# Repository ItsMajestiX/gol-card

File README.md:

# Game of Life Card
A custom PCB that uses a TI MSP430 MCU to run a finite version of Conway's Game of Life on an ePaper display.
# Documentation
To read about the development of this project, please visit [this project's site](https://itsmajestix.github.io/gol-card/). If you want to view the site's source, go to the `gol_card_docs` directory to find many markdown files documenting the development process of this project.
# Building
This project will build on Zig 0.14.1. Once you have downloaded it, run `zig build run` to try out the desktop simulator.

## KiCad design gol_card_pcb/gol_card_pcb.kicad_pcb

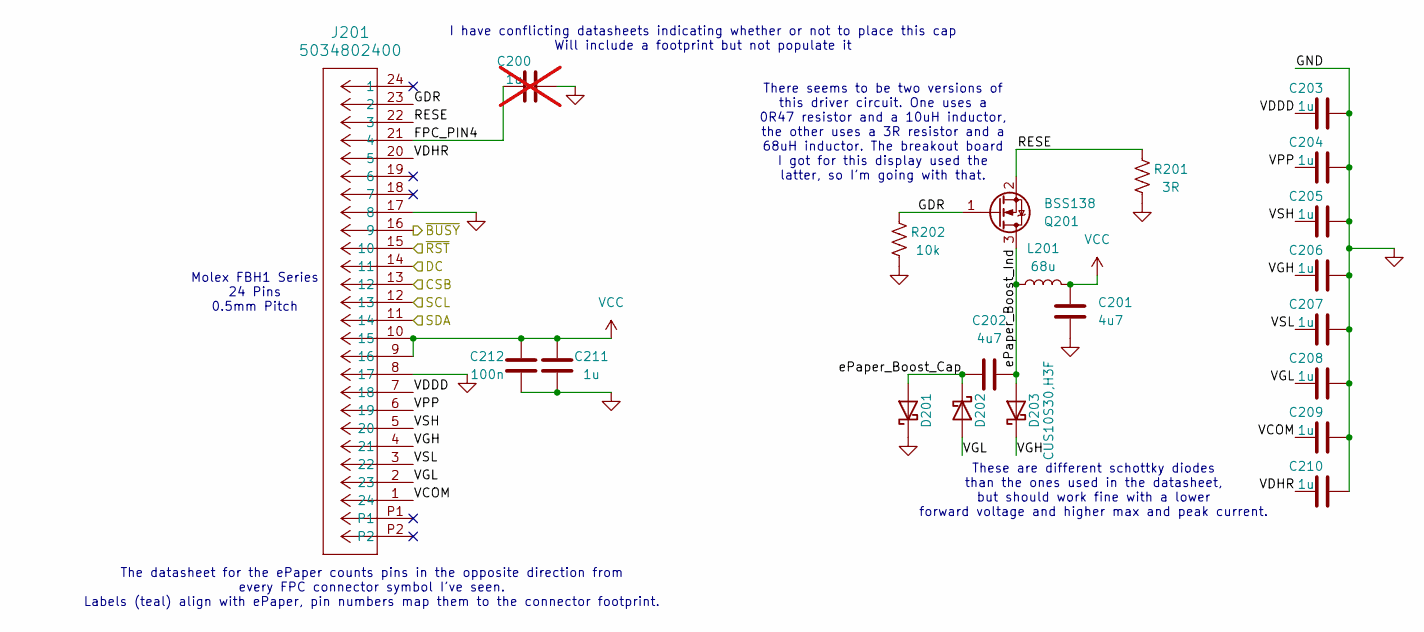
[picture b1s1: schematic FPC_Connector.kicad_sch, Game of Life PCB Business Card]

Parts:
C200: 1u; C_0603_1608Metric; not fitted
C201, C202: 4u7; C_0805_2012Metric
C203, C204, C205, C206, C207, C208, C209, C210, C211: 1u; C_0603_1608Metric
C212: 100n; C_0603_1608Metric
D201, D202, D203: CUS10S30,H3F; D_SOD-323
J201: 5034802400; CON_5034802400_MOL
L201: 68u; L_Taiyo-Yuden_NR-80xx
Q201: BSS138; SOT-23
R201: 3R; R_0805_2012Metric
R202: 10k; R_0402_1005Metric

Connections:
/FPC_Connector/CSB: J201.13 (12); also elsewhere on the board
/FPC_Connector/DC: J201.14 (11); also elsewhere on the board
/FPC_Connector/FPC_PIN4: C200.1, J201.21 (4)
/FPC_Connector/GDR: J201.23 (2), Q201.1 (G), R202.2
/FPC_Connector/RESE: J201.22 (3), Q201.2 (S), R201.1
/FPC_Connector/SCL: J201.12 (13); also elsewhere on the board
/FPC_Connector/SDA: J201.11 (14); also elsewhere on the board
/FPC_Connector/VCOM: C209.1, J201.1 (24)
/FPC_Connector/VDDD: C203.1, J201.7 (18)
/FPC_Connector/VDHR: C210.1, J201.20 (5)
/FPC_Connector/VGH: C206.1, D203.1 (K), J201.4 (21)
/FPC_Connector/VGL: C208.1, D202.2 (A), J201.2 (23)
/FPC_Connector/VPP: C204.1, J201.6 (19)
/FPC_Connector/VSH: C205.1, J201.5 (20)
/FPC_Connector/VSL: C207.1, J201.3 (22)
/FPC_Connector/ePaper_Boost_Cap: C202.2, D201.2 (A), D202.1 (K)
/FPC_Connector/ePaper_Boost_Ind: C202.1, D203.2 (A), L201.1, Q201.3 (D)
/FPC_Connector/~BUSY: J201.16 (9); also elsewhere on the board
/FPC_Connector/~RST: J201.15 (10); also elsewhere on the board
GND: C200.2, C201.2, C203.2, C204.2, C205.2, C206.2, C207.2, C208.2, C209.2, C210.2, C211.2, C212.2, D201.1 (K), J201.8 (17), J201.17 (8), R201.2, R202.1; also elsewhere on the board
VCC: C201.1, C211.1, C212.1, J201.9 (16), J201.10 (15), L201.2; also elsewhere on the board

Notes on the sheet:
The datasheet for the ePaper counts pins in the opposite direction from every FPC connector symbol I've seen. Labels (teal) align with ePaper, pin numbers map them to the connector footprint.
Molex FBH1 Series 24 Pins 0.5mm Pitch
These are different schottky diodes than the ones used in the datasheet, but should work fine with a lower forward voltage and higher max and peak current.
There seems to be two versions of this driver circuit. One uses a 0R47 resistor and a 10uH inductor, the other uses a 3R resistor and a 68uH inductor. The breakout board I got for this display used the latter, so I'm going with that.
I have conflicting datasheets indicating whether or not to place this cap Will include a footprint but not populate it

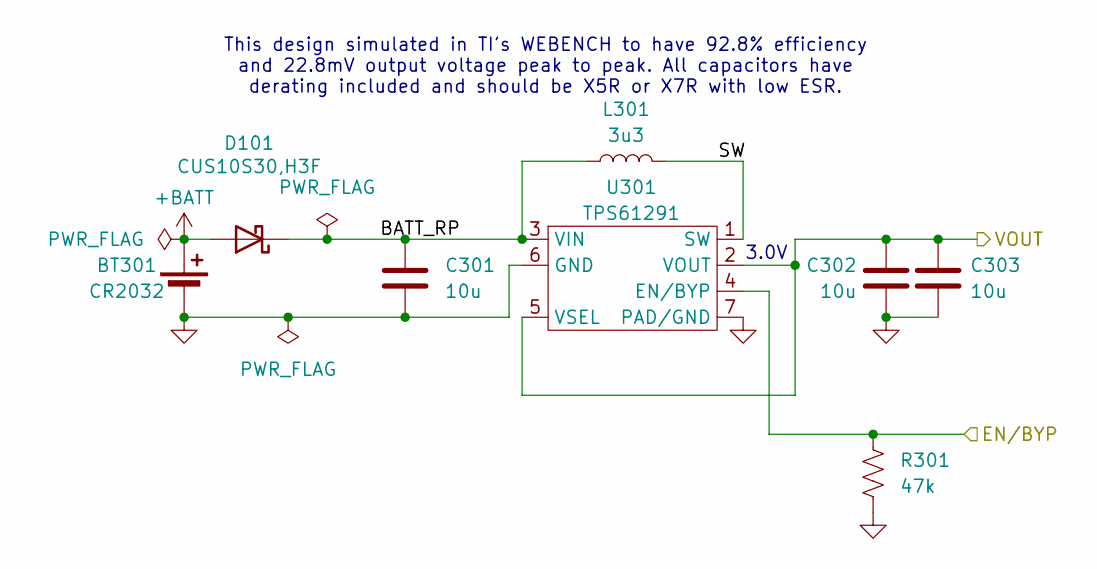
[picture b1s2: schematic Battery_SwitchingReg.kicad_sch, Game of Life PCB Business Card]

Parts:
BT301: CR2032; BatteryHolder_Keystone_3002_1x2032
C301, C302, C303: 10u; C_0603_1608Metric
D101: CUS10S30,H3F; D_SOD-323
L301: 3u3; L_Taiyo-Yuden_NR-50xx
R301: 47k; R_0402_1005Metric
U301: TPS61291; WSON-6-1EP_2x2mm_P0.65mm_EP1x1.6mm

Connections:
+BATT: BT301.1 (+), D101.2 (A)
/Battery_SwitchingReg/BATT_RP: C301.1, D101.1 (K), L301.1, U301.3 (VIN)
/Battery_SwitchingReg/EN/BYP: R301.1, U301.4 (EN/BYP); also elsewhere on the board
/Battery_SwitchingReg/SW: L301.2, U301.1 (SW)
/MCU/PWR_BOARD: C302.1, C303.1, U301.2 (VOUT), U301.5 (VSEL); also elsewhere on the board
GND: BT301.2 (-), C301.2, C302.2, C303.2, R301.2, U301.6 (GND), U301.7 (PAD/GND); also elsewhere on the board

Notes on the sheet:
3.0V
This design simulated in TI's WEBENCH to have 92.8% efficiency and 22.8mV output voltage peak to peak. All capacitors have derating included and should be X5R or X7R with low ESR.

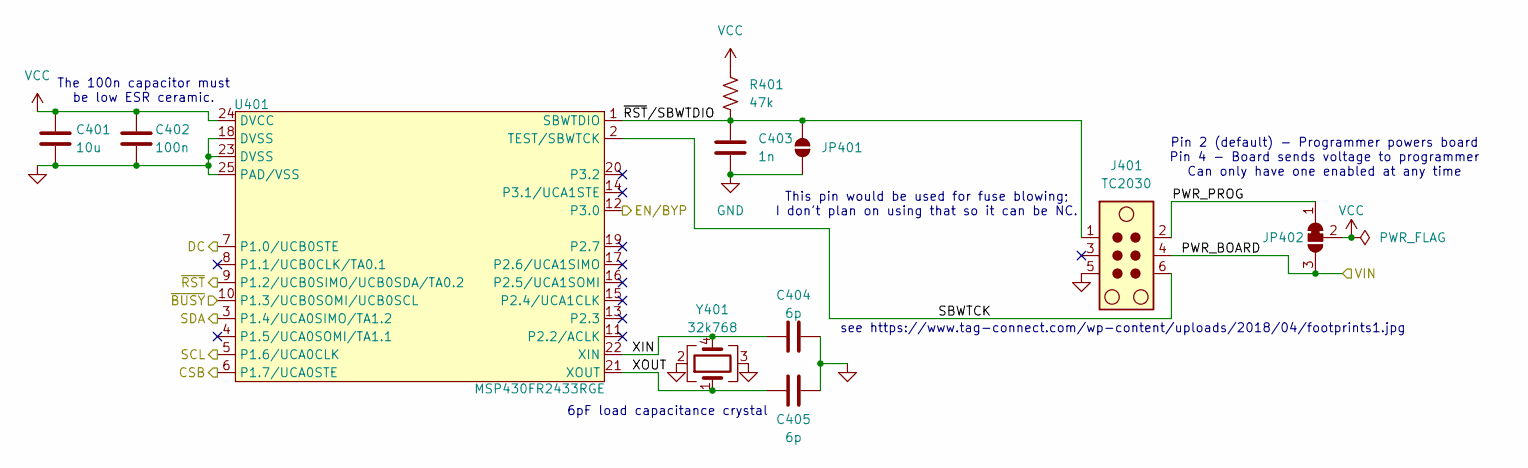
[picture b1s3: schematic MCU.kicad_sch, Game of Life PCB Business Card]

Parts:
C401: 10u; C_0603_1608Metric
C402: 100n; C_0603_1608Metric
C403: 1n; C_0402_1005Metric
C404, C405: 6p; C_0402_1005Metric
J401: TC2030; TC2030_Legs_PTH
JP401: SolderJumper_2_Open; SolderJumper-2_P1.3mm_Open_TrianglePad1.0x1.5mm
JP402: SolderJumper_3_Bridged12; SolderJumper-3_P1.3mm_Bridged12_Pad1.0x1.5mm_NumberLabels
R401: 47k; R_0402_1005Metric
U401: MSP430FR2433RGE; Texas_RGE0024H_VQFN-24-1EP_4x4mm_P0.5mm_EP2.7x2.7mm
Y401: 32k768; Crystal_SMD_Abracon_ABS25-4Pin_8.0x3.8mm

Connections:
/Battery_SwitchingReg/EN/BYP: U401.12 (P3.0); also elsewhere on the board
/FPC_Connector/CSB: U401.6 (P1.7/UCA0STE); also elsewhere on the board
/FPC_Connector/DC: U401.7 (P1.0/UCB0STE); also elsewhere on the board
/FPC_Connector/SCL: U401.5 (P1.6/UCA0CLK); also elsewhere on the board
/FPC_Connector/SDA: U401.3 (P1.4/UCA0SIMO/TA1.2); also elsewhere on the board
/FPC_Connector/~BUSY: U401.10 (P1.3/UCB0SOMI/UCB0SCL); also elsewhere on the board
/FPC_Connector/~RST: U401.9 (P1.2/UCB0SIMO/UCB0SDA/TA0.2); also elsewhere on the board
/MCU/PWR_BOARD: J401.4, JP402.3 (B); also elsewhere on the board
/MCU/PWR_PROG: J401.2, JP402.1 (A)
/MCU/SBWTCK: J401.6, U401.2 (TEST/SBWTCK)
/MCU/XIN: C404.1, U401.22 (XIN), Y401.4
/MCU/XOUT: C405.1, U401.21 (XOUT), Y401.1
/MCU/~RST/SBWTDIO: C403.1, J401.1, JP401.1 (A), R401.2, U401.1 (SBWTDIO)
GND: C401.2, C402.2, C403.2, C404.2, C405.2, J401.5, JP401.2 (B), U401.18 (DVSS), U401.23 (DVSS), U401.25 (PAD/VSS), Y401.2, Y401.3; also elsewhere on the board
VCC: C401.1, C402.1, JP402.2 (C), R401.1, U401.24 (DVCC); also elsewhere on the board

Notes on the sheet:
The 100n capacitor must be low ESR ceramic.
see https://www.tag-connect.com/wp-content/uploads/2018/04/footprints1.jpg
Pin 2 (default) - Programmer powers board Pin 4 - Board sends voltage to programmer Can only have one enabled at any time
This pin would be used for fuse blowing; I don't plan on using that so it can be NC.
6pF load capacitance crystal

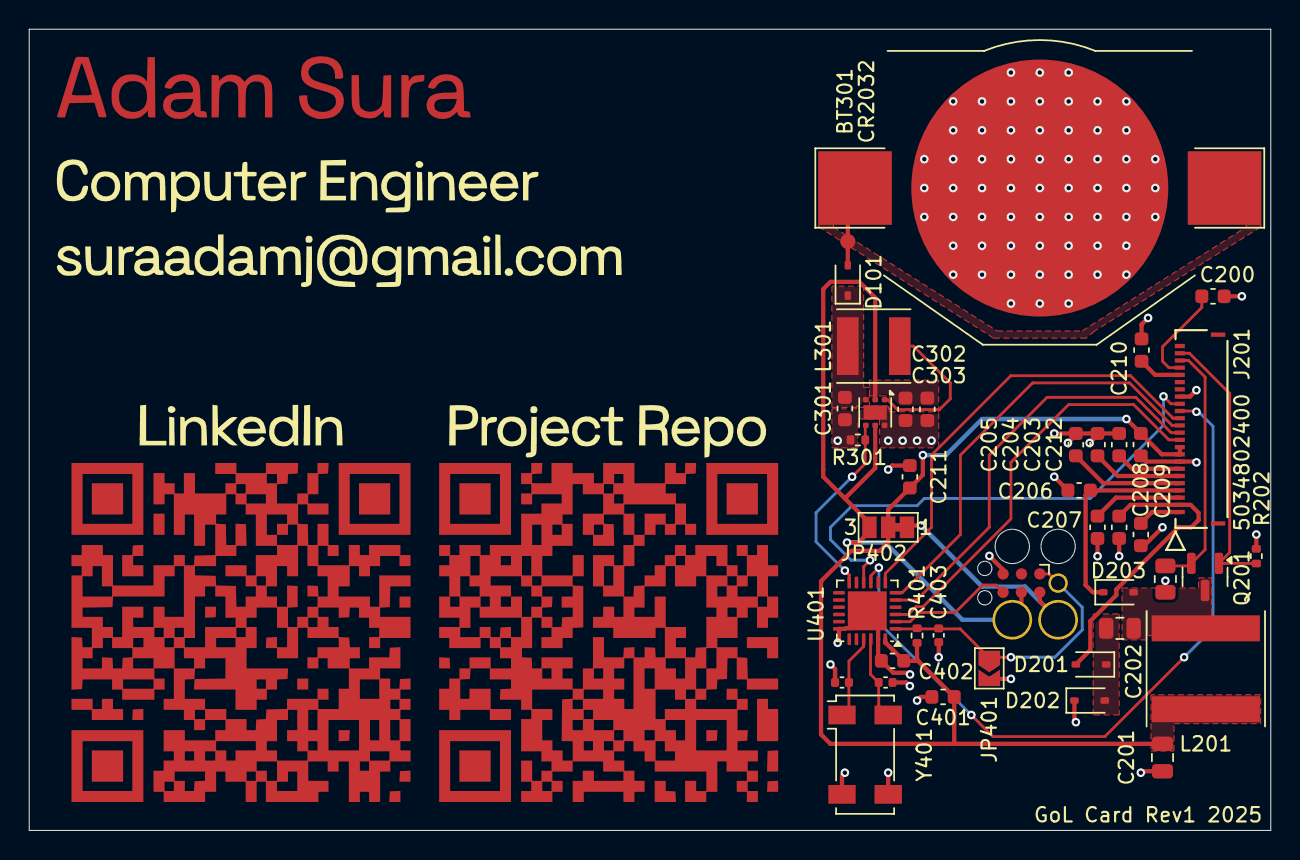
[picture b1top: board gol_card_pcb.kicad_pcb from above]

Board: 2 copper layers, 86.0 x 55.5 mm, 40 parts (0 on the bottom side), 31 nets.

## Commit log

2024-11-29 get something (not working) down
2024-11-30 fix undefined memory issue, but rules are not being followed
2024-11-30 successfully (?) simulate GoL
2024-12-01 writeup about getting the simulator working
2024-12-01 switch to 9bit lookup, unit tests for shiftInRight and stepRow
2024-12-01 add a test for updateBoard
2024-12-04 change to u16 for lookup, massive speedup
2024-12-05 add variety of time scales + step functionality
2024-12-05 implement saving state to file
2024-12-08 new writing, change variable name
2024-12-08 get some hardware abstraction, but it feels bad
2024-12-12 will go with this for now, may change later
2024-12-20 update zig, switch to local deps
2024-12-20 build msp430 assembly
2024-12-23 stub hal, add code to run a step of the game
2024-12-27 more writing, minor code changes
2024-12-28 start working on adding toolchain management to build.zig
2024-12-31 get mspdebug to compile and run (many asterisks)
2024-12-31 install mspdebug in correct directory (zig-out/bin)
2025-01-02 get a downloader script going, more writing
2025-01-02 get mspdebug to take arguments from zig cli
2025-01-02 add comments to build file and downloader, use downloader in build file
2025-01-03 work on unzipping
2025-01-04 become capable of downloading and extracting all build dependencies
2025-01-04 achieve a working .elf build w/ proper linker files
2025-01-09 get step to run on msp
2025-01-10 add loop detector + board reset
2025-01-16 work on eink irq, commit to find error
2025-01-16 fix offset bug in CFI remover
2025-01-16 change HAL, remove need for linking hw multiply on msp430
2025-01-16 maybe (unlikely) get the whole display process implemented
2025-01-28 commit changes before debugging
2025-01-28 actually export interrupt handlers
2025-01-28 remove temp slice from spi irq
2025-01-30 avoid accessing zero length slices
2025-02-03 LETS GOOOOO
2025-02-03 cooking is almost complete
2025-02-04 remove test busy wait
2025-02-05 add untested ADC code
2025-02-05 get the ADC to work, use it to seed the RNG I hope that the pointer magic in hal-embedded to turn the u256 into a [4]u64 works...
2025-02-09 get five minute timer working
2025-02-09 add chip specific options
2025-02-10 comment some code
2025-02-10 last minute documentation
2025-02-10 add GPLv3
2025-08-29 update code to work with finished board
2025-09-16 update licence, add PCB, add new docs
2025-09-16 add website files
2025-09-16 readd the readme
2025-09-16 github pages requires folder to be named docs
2025-09-16 remove submodules, update to Zig 0.14.1, update raylib and raylib-zig
2025-09-16 unstaged changes, oops
2025-09-16 update files with website url
